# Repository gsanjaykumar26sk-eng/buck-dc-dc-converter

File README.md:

#  Classical Buck DC-DC Converter (30V → 15V, 30W, 50kHz)

> Mini Project — BEEE301L Power Electronics | VIT Chennai | Winter Semester 2025-26
> Faculty: Dr. M. Prabhakar 

---

## Overview

A classical Buck (step-down) DC-DC converter designed to convert a 30V input to a regulated 15V output at 30W, switching at 50kHz. The project covers the complete design flow — mathematical design, MATLAB/Simulink simulation, LTspice verification, and PCB fabrication using KiCad 9.0.

---

##  Specifications

| Parameter | Value |
|-----------|-------|
| Input Voltage | 30 V |
| Output Voltage | 15 V |
| Output Power | 30 W |
| Output Current | 2 A |
| Switching Frequency | 50 kHz |
| Duty Cycle | 0.5 |
| Operating Mode | Continuous Conduction Mode (CCM) |

---

##  Components

| Component | Part | Rating |
|-----------|------|--------|
| MOSFET | IRF540N | 100V, 33A |
| Diode | MBR1060 | 60V, 10A |
| Gate Driver | TLP250 | Opto-isolated |
| Inductor | Coilcraft RFB0810-221L | 220 µH |
| Capacitor | Nichicon UPM1E100MHD | 10 µF / 25V |
| Load | — | 7.5 Ω |
| PWM Source | Arduino | 50kHz via Timer1 |

---

##  Design Equations

```
Duty Cycle:   D = Vout / Vin = 15 / 30 = 0.5

Inductor:     L = (Vin - Vout) × D / (ΔiL × f)  →  220 µH selected

Capacitor:    C = ΔiL / (8 × f × ΔVout)  →  10 µF selected
```

---

##  Simulation

Simulated in **MATLAB/Simulink** and **LTspice** to verify:
- Output voltage regulation at 15V
- Inductor current waveform in CCM
- Output voltage ripple under load
- MOSFET switching transitions

 Simulation files → `/simulation/`

**To run MATLAB/Simulink model:**
1. Open MATLAB (R2023a or later)
2. Open `buck_converter_simulation.slx`
3. Run simulation (Ctrl+T) and view scope blocks

---

##  PCB Design (KiCad 9.0)

Designed with attention to:
- Power trace width calculated for 2A
- Ground plane for noise reduction
- Short gate drive traces to minimise switching noise
- Component placement for thermal management

 KiCad files → `/pcb/`

**PCB status:** Fabricated  | Tested  (pending)

---

##  Arduino PWM Gate Drive

```cpp
// 50kHz PWM via Timer1 on Pin 9
// 16MHz / (1 × (319+1)) = 50kHz

void setup() {
  TCCR1A = _BV(COM1A1) | _BV(WGM11);
  TCCR1B = _BV(WGM13) | _BV(WGM12) | _BV(CS10);
  ICR1  = 319;   // Sets 50kHz
  OCR1A = 159;   // 50% duty cycle
}

void loop() { } // Timer1 runs autonomously
```

---

##  Repository Structure

```
buck-dc-dc-converter/
├── README.md
├── simulation/
│   ├── buck_converter_simulation.slx   ← MATLAB/Simulink
│   └── buck_converter.asc              ← LTspice
├── pcb/
│   ├── buck_converter.kicad_pro
│   ├── buck_converter.kicad_sch
│   ├── buck_converter.kicad_pcb
│   └── gerber/
├── arduino/
│   └── pwm_gate_drive.ino
└── docs/
    └── project_report.pdf
```

---

##  Key Learnings

- Buck converter operation in CCM and duty cycle control
- Inductor and capacitor design from equations
- MATLAB/Simulink and LTspice simulation workflows
- PCB design: trace width, ground planes, layout for power electronics
- Timer register programming in Arduino for precise PWM

---

##  Team

| Name | Reg. No. |
|------|----------|
| Sanjay Kumar G | 24BEE1256 |
| Selva Krishna SJ | 24BEE1017 |

---

**Sanjay Kumar G** · B.Tech EEE, VIT Chennai  
[LinkedIn](https://www.linkedin.com/in/sanjay-kumar-g-933073333) · [GitHub](https://github.com/gsanjaykumar26sk-eng)

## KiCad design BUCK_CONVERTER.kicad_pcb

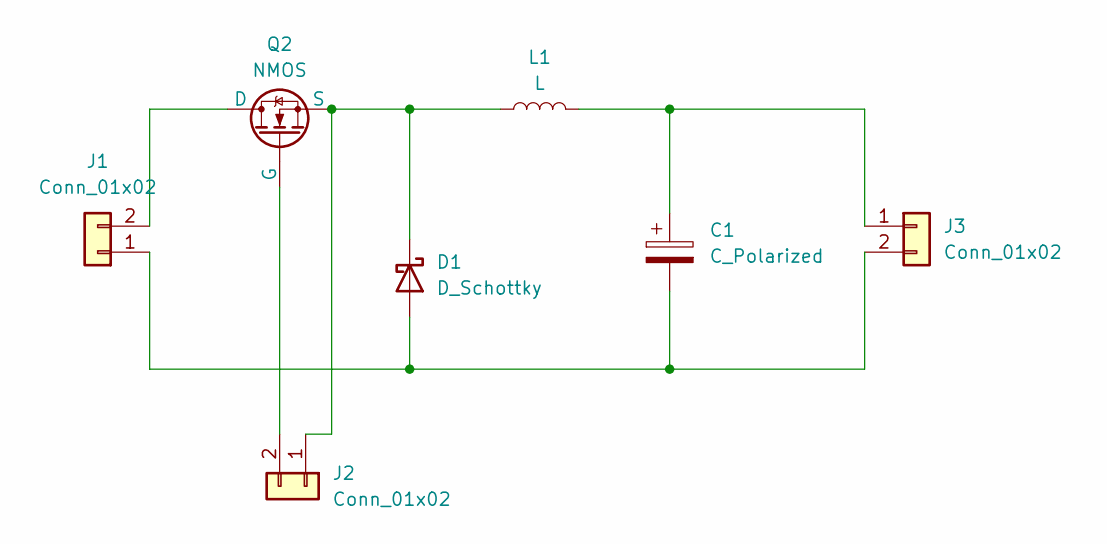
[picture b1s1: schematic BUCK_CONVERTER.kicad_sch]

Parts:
C1: C_Polarized; CP_Radial_D8.0mm_P3.50mm
D1: D_Schottky; D_DO-201AD_P15.24mm_Horizontal
J1, J2, J3: Conn_01x02; TerminalBlock_Phoenix_MKDS-1,5-2_1x02_P5.00mm_Horizontal
L1: L; L_Radial_D12.0mm_P5.00mm_Fastron_11P
Q2: NMOS; TO-220-3_Vertical

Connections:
unnamed: C1.2, D1.2 (A), J1.1, J3.2
unnamed: D1.1 (K), J2.1, L1.1, Q2.3 (S)
unnamed: J1.2, Q2.1 (D)
unnamed: J2.2, Q2.2 (G)
unnamed: C1.1, J3.1, L1.2

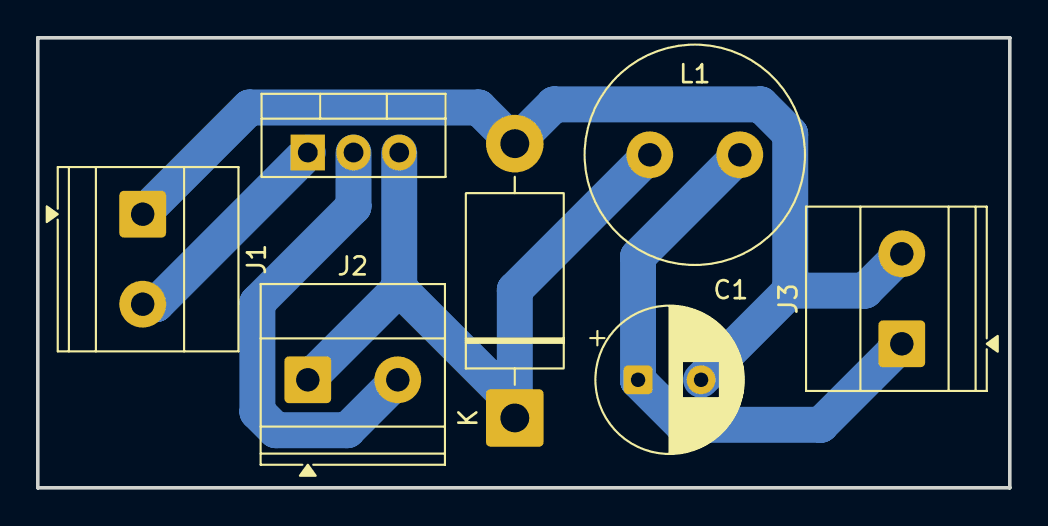
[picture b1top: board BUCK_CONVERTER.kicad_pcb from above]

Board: 2 copper layers, 54.0 x 25.0 mm, 7 parts (0 on the bottom side), 5 nets.
